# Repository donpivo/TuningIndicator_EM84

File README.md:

Description: https://retronics.no/2024/02/22/diy-digital-em84-magic-eye-replacement/

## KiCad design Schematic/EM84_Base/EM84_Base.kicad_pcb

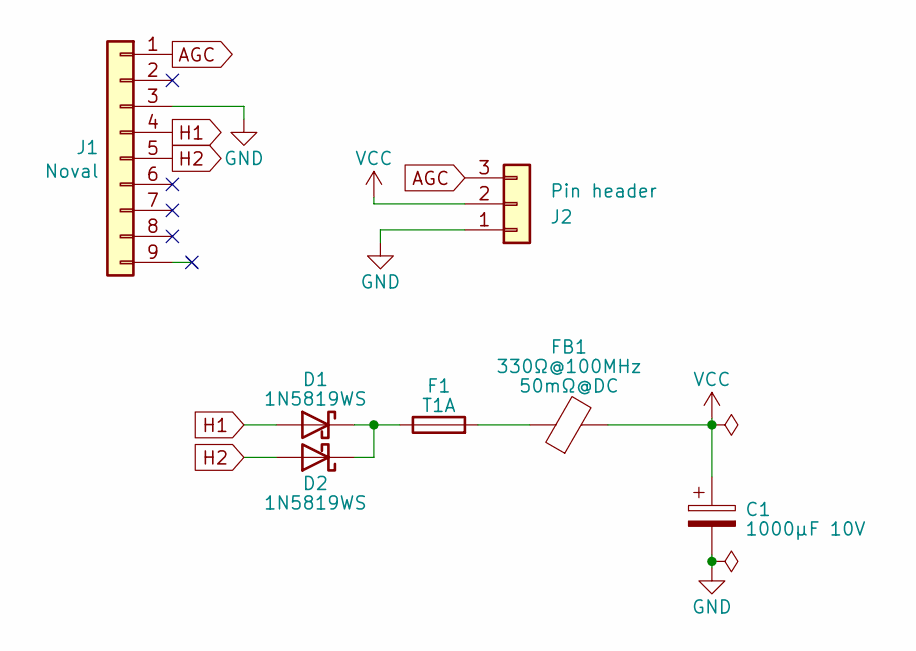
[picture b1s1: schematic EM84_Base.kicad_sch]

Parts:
C1: 1000µF 10V; CP_Radial_D8.0mm_P3.50mm_EM84
D1, D2: 1N5819WS; D_SOD-323_HandSoldering
F1: T1A; Fuse_1206_3216Metric
FB1: 330Ω@100MHz; L_0805_2012Metric_Pad1.15x1.40mm_HandSolder
J1: Noval; EM84_Socket
J2: Pin header; PinSocket_1x03_P2.54mm_Vertical_alt

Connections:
GND: C1.2, J1.3, J2.1
H1: D1.2 (A), J1.4
H2: D2.2 (A), J1.5
unnamed: D1.1 (K), D2.1 (K), F1.1
unnamed: F1.2, FB1.1
SIG: J1.1, J2.3
VCC: C1.1, FB1.2, J2.2

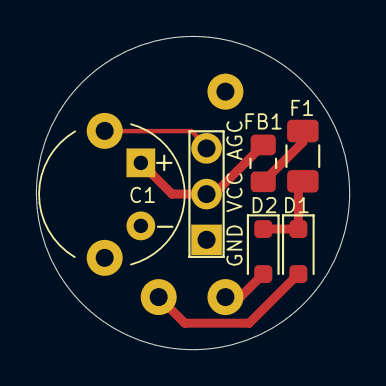
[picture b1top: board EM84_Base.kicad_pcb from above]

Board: 2 copper layers, 17.4 x 17.4 mm, 7 parts (0 on the bottom side), 7 nets.

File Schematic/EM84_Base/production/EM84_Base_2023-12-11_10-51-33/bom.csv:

Designator,Footprint,Quantity,Value,LCSC Part #
C1,CP_Radial_D8.0mm_P3.50mm_EM84,1,1000µF 16V,
"D1, D2",D_SOD-323_HandSoldering,2,1N5819WS,
"F1, F2",0805,2,T1A,
J1,EM84_Socket,1,Noval,
J2,PinSocket_1x03_P2.54mm_Vertical_alt,1,Pin header,

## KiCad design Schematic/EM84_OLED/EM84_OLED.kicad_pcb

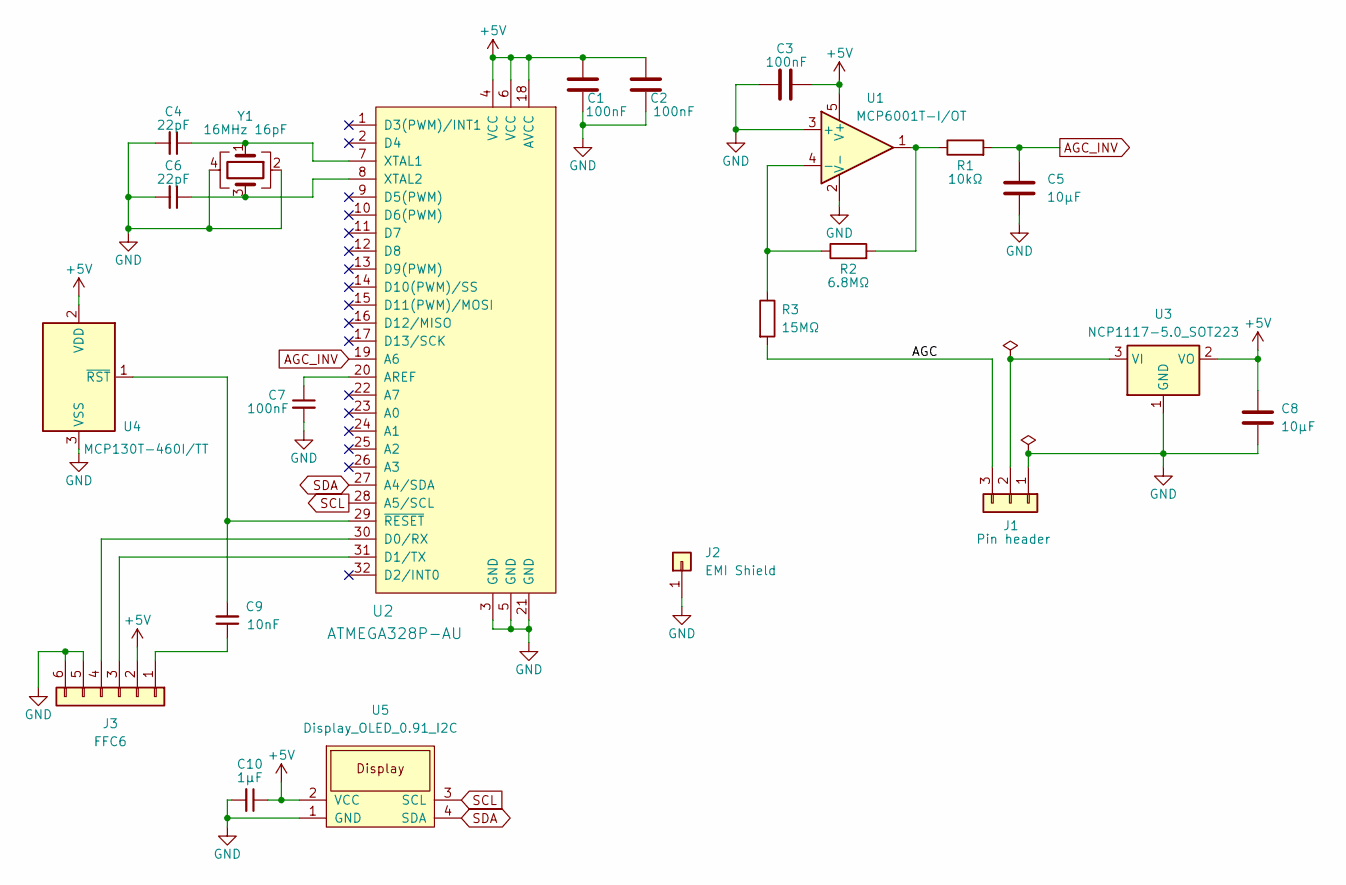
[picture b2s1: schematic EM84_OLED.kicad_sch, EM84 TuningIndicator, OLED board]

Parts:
C1, C2, C3, C7: 100nF; C_0603_1608Metric_Pad1.08x0.95mm_HandSolder
C4, C6: 22pF; C_0603_1608Metric_Pad1.08x0.95mm_HandSolder
C5, C8: 10µF; C_0603_1608Metric_Pad1.08x0.95mm_HandSolder
C9: 10nF; C_0603_1608Metric_Pad1.08x0.95mm_HandSolder
C10: 1µF; C_0603_1608Metric_Pad1.08x0.95mm_HandSolder
J1: Pin header; PinHeader_1x03_P2.54mm_Horizontal_Alt
J2: EMI Shield; EMI_Shield_MS192-10S
J3: FFC6; FFC_0527450697
R1: 10kΩ; R_0603_1608Metric_Pad0.98x0.95mm_HandSolder
R2: 6.8MΩ; R_0603_1608Metric_Pad0.98x0.95mm_HandSolder
R3: 15MΩ; R_0603_1608Metric_Pad0.98x0.95mm_HandSolder
U1: MCP6001T-I/OT; SOT-23-5
U2: ATMEGA328P-AU; TQFP-32_7x7mm_P0.8mm
U3: NCP1117-5.0_SOT223; SOT-223-3_TabPin2
U4: MCP130T-460I/TT; SOT-23
U5: Display_OLED_0.91_I2C; 0.91-OLED-4pin-128x32
Y1: 16MHz 16pF; Crystal_SMD_SeikoEpson_TSX3225-4Pin_3.2x2.5mm

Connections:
+5V: C1.2, C2.2, C3.2, C8.1, C10.1, J3.2, U1.5 (V+), U2.4 (VCC), U2.6 (VCC), U2.18 (AVCC), U3.2 (VO), U4.2 (VDD), U5.2 (VCC)
/AGC: J1.3, R3.2
AGC_INV: C5.1, R1.2, U2.19 (A6)
GND: C1.1, C2.1, C3.1, C4.2, C5.2, C6.2, C7.2, C8.2, C10.2, J1.1, J2.1, J3.5, J3.6, U1.2 (V-), U1.3 (+), U2.3 (GND), U2.5 (GND), U2.21 (GND), U3.1 (GND), U4.3 (VSS), U5.1 (GND), Y1.2, Y1.4
unnamed: J1.2, U3.3 (VI)
unnamed: C9.1, J3.1
unnamed: J3.3, U2.31 (D1/TX)
unnamed: J3.4, U2.30 (D0/RX)
unnamed: R1.1, R2.2, U1.1
unnamed: R2.1, R3.1, U1.4 (-)
unnamed: C7.1, U2.20 (AREF)
unnamed: C4.1, U2.7 (XTAL1), Y1.1
unnamed: C6.1, U2.8 (XTAL2), Y1.3
unnamed: C9.2, U2.29 (~RESET), U4.1 (~RST)
SCL: U2.28 (A5/SCL), U5.3 (SCL)
SDA: U2.27 (A4/SDA), U5.4 (SDA)

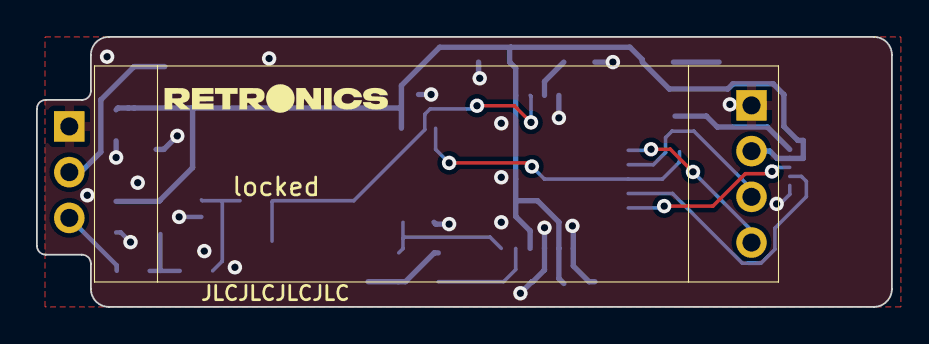
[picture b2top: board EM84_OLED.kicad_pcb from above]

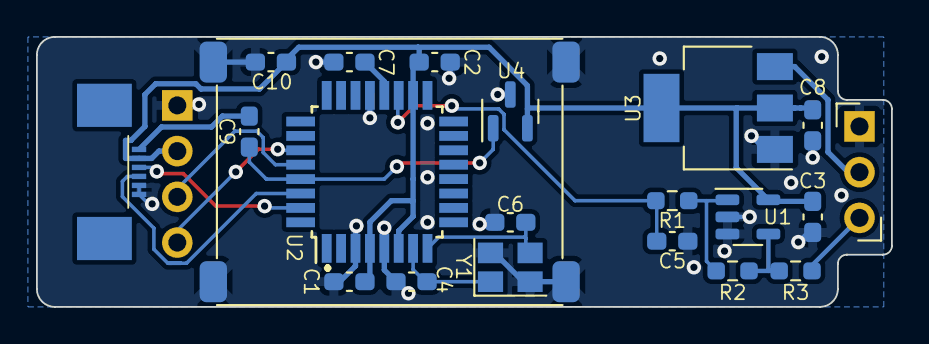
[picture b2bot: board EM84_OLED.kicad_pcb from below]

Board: 2 copper layers, 47.5 x 15.0 mm, 22 parts (21 on the bottom side), 16 nets.

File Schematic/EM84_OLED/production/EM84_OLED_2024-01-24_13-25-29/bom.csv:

Designator,Footprint,Quantity,Value,LCSC Part #
"C1, C2, C3, C7",0603,4,100nF,
C10,0603,1,1µF,
"C4, C6",0603,2,22pF,
"C5, C8",0603,2,10µF,
C9,0603,1,10nF,
J1,PinHeader_1x03_P2.54mm_Horizontal_Alt,1,Pin header,
J2,EMI_Shield_MS192-10S,1,EMI Shield,
J3,FFC_0527450697,1,FFC6,
R1,0603,1,10kΩ,
R2,0603,1,6.8MΩ,
R3,0603,1,15MΩ,
U1,SOT-23-5,1,MCP6001T-I/OT,
U2,TQFP-32_7x7mm_P0.8mm,1,ATMEGA328P-AU,
U3,SOT-223-3_TabPin2,1,NCP1117-5.0_SOT223,
U4,SOT-23,1,MCP130T-460I/TT,
U5,0.91-OLED-4pin-128x32,1,Display_OLED_0.91_I2C,
Y1,Crystal_SMD_SeikoEpson_TSX3225-4Pin_3.2x2.5mm,1,16MHz 16pF,

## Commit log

2023-12-11 Updated PCB layout
2024-02-22 File cleanup
2024-02-22 Added README
